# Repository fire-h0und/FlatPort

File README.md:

# FlatPort
Teensy 2.0 Risc-V dropin Arduino promicro lookalike with special features. The chip I used is [GD32 VF 103 CBT6](https://www.gigadevice.com/product/mcu/mcus-product-selector/gd32vf103cbt6) from Giga Device. 

It has a in-plane Type-C USB receptacle - it does not show much but it doubles as a full featured Type-C port - in this case a reversible USB 2.0 spec port only.

It also features in-plane Reset and Boot0 tasters - they are shorted by touching with a pointy conductive/metal object.<br>
  Do note they are not to be touched mutually by a same metal object: one shorts pin Boot0 to ground the other pulls the reset pin to Vcc.<br>
  In effect this means one of the contacts is gound and the other is Vcc - shorting them mutually would blow the fuse!

I picked to make this project for the alleged compatibility with QMK firmware - to be a future keyboard daughter board.
As I get to that point expect more updates here, it is on my ever growing TODO list :o}

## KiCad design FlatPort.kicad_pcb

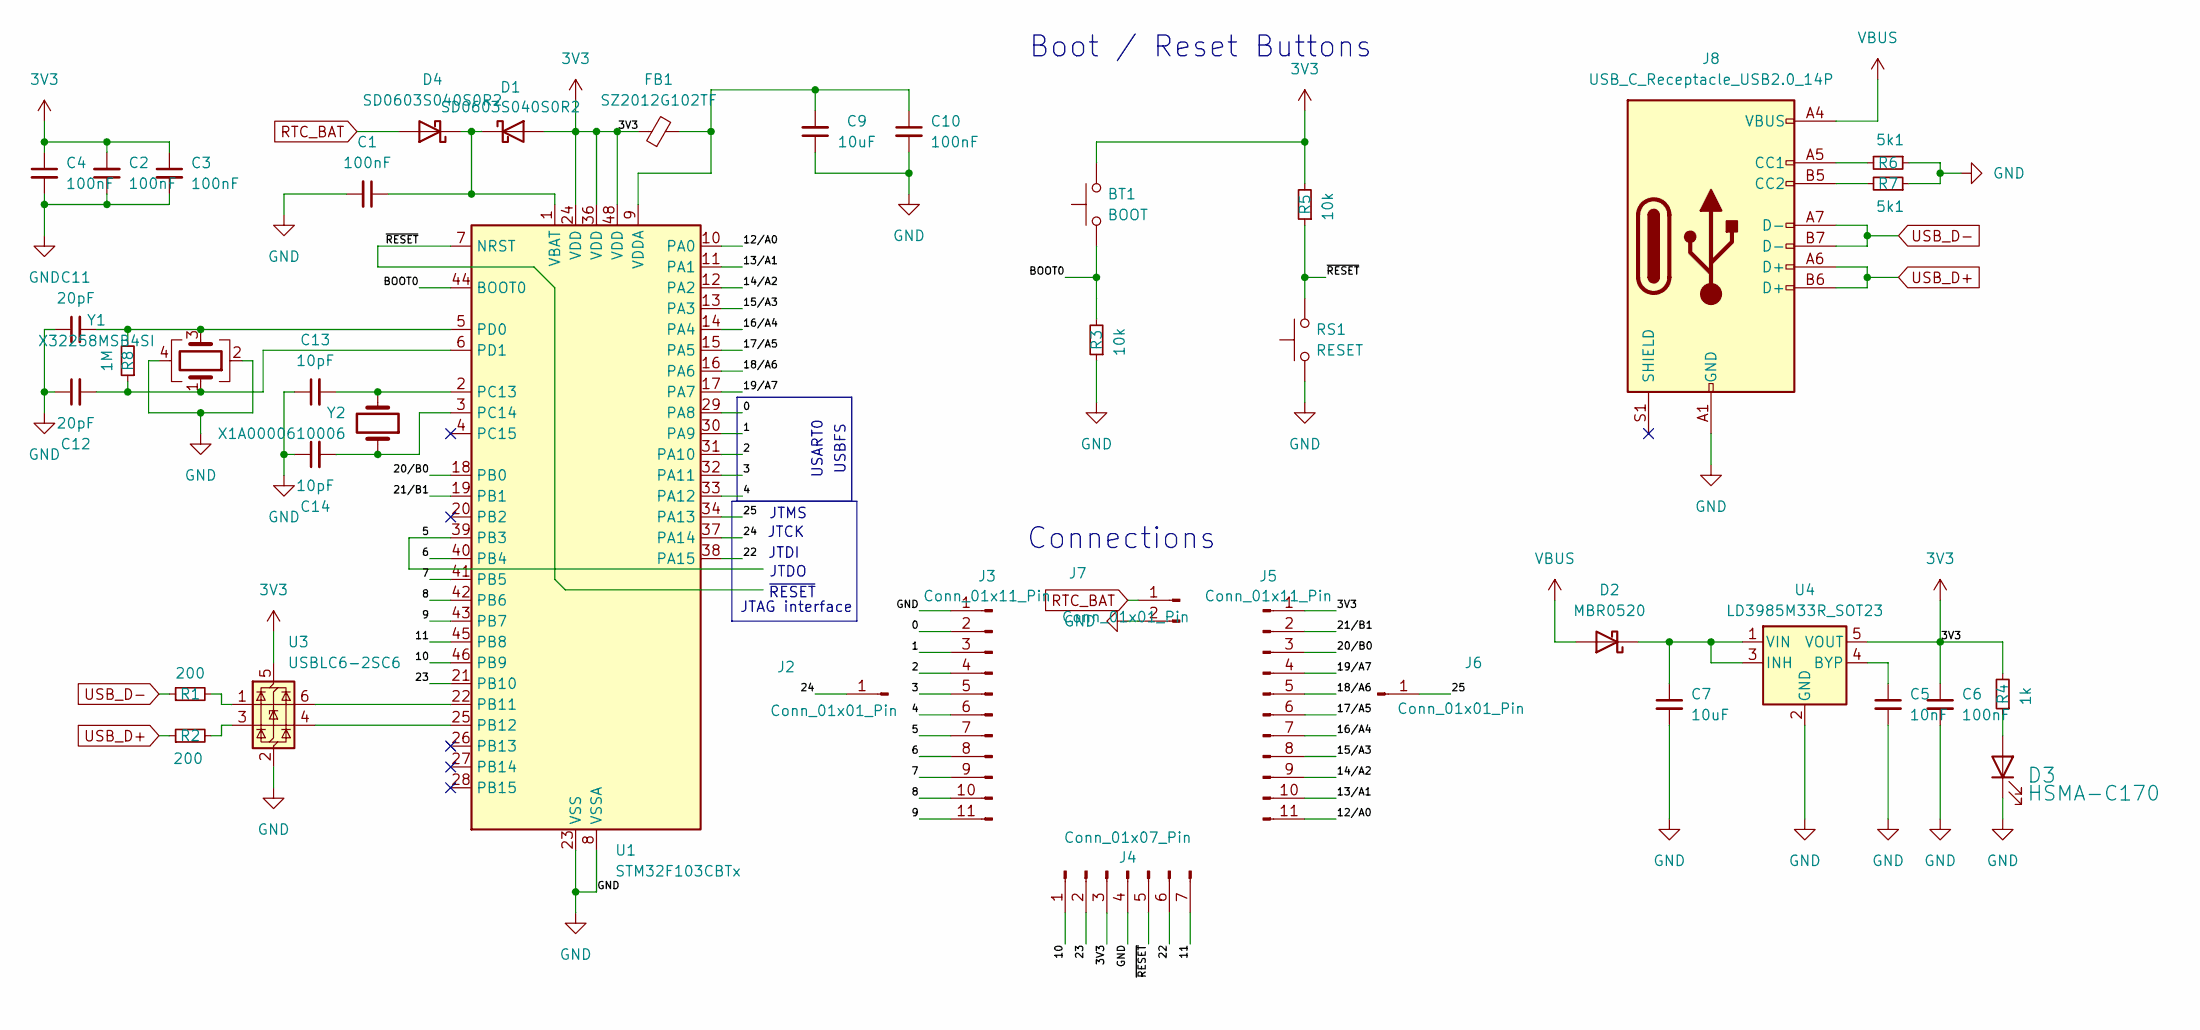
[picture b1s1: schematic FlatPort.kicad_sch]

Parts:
BT1: BOOT; Switch_Hole_1.0mm
C1, C2, C3, C4, C6, C10: 100nF; C_0402_1005Metric
C5: 10nF; C_0402_1005Metric
C7, C9: 10uF; C_0402_1005Metric
C11, C12: 20pF; C_0402_1005Metric
C13, C14: 10pF; C_0402_1005Metric
D1, D4: SD0603S040S0R2; D_0603_1608Metric
D2: MBR0520; D_SOD-123
D3: HSMA-C170; LED_0805_2012Metric
FB1: SZ2012G102TF; L_0805_2012Metric; LCSC Part# C1002
J2, J6: Conn_01x01_Pin; PinHeader_1x01_P2.54mm_Vertical
J3, J5: Conn_01x11_Pin; PinHeader_1x11_P2.54mm_Vertical
J4: Conn_01x07_Pin; PinHeader_1x07_P2.54mm_Vertical
J7: Conn_01x01_Pin; PinHeader_1x02_P1.27mm_Vertical
J8: USB_C_Receptacle_USB2.0_14P; TypeC_PCB_cutout
R1, R2: 200; R_0402_1005Metric
R3, R5: 10k; R_0402_1005Metric
R4: 1k; R_0402_1005Metric
R6, R7: 5k1; R_0402_1005Metric
R8: 1M; R_0402_1005Metric
RS1: RESET; Switch_Hole_1.0mm
U1: STM32F103CBTx; LQFP-48_7x7mm_P0.5mm
U3: USBLC6-2SC6; SOT-23-6
U4: LD3985M33R_SOT23; SOT-23-5
Y1: X32258MSB4SI; Crystal_SMD_3225-4Pin_3.2x2.5mm
Y2: X1A0000610006; Crystal_SMD_2012-2Pin_2.0x1.2mm

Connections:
3V3: BT1.2, C2.2, C3.1, C4.1, C6.1, D1.2 (A), FB1.1, J4.3, J5.1, R4.2, R5.2, U1.24 (VDD), U1.36 (VDD), U1.48 (VDD), U3.5 (VBUS), U4.5 (VOUT)
/0: J3.2, U1.29 (PA8)
/1: J3.3, U1.30 (PA9)
/2: J3.4, U1.31 (PA10)
/3: J3.5, U1.32 (PA11)
/4: J3.6, U1.33 (PA12)
/5: J3.7, U1.39 (PB3)
/6: J3.8, U1.40 (PB4)
/7: J3.9, U1.41 (PB5)
/8: J3.10, U1.42 (PB6)
/9: J3.11, U1.43 (PB7)
/10: J4.1, U1.46 (PB9)
/11: J4.7, U1.45 (PB8)
/12/A0: J5.11, U1.10 (PA0)
/13/A1: J5.10, U1.11 (PA1)
/14/A2: J5.9, U1.12 (PA2)
/15/A3: J5.8, U1.13 (PA3)
/16/A4: J5.7, U1.14 (PA4)
/17/A5: J5.6, U1.15 (PA5)
/18/A6: J5.5, U1.16 (PA6)
/19/A7: J5.4, U1.17 (PA7)
/20/B0: J5.3, U1.18 (PB0)
/21/B1: J5.2, U1.19 (PB1)
/22: J4.6, U1.38 (PA15)
/23: J4.2, U1.21 (PB10)
/24: J2.1, U1.37 (PA14)
/25: J6.1, U1.34 (PA13)
/BOOT0: BT1.1, R3.2, U1.44 (BOOT0)
/~RESET: J4.5, R5.1, RS1.2, U1.7 (NRST)
GND: C1.2, C2.1, C3.2, C4.2, C5.2, C6.2, C7.2, C9.1, C10.2, C11.1, C12.1, C13.1, C14.1, D3.1 (K), J3.1, J4.4, J7.2, J8.A1 (GND), J8.A12 (GND), J8.B1 (GND), J8.B12 (GND), R3.1, R6.1, R7.1, RS1.1, U1.8 (VSSA), U1.23 (VSS), U1.35 (VSS), U1.47 (VSS), U3.2 (GND), U4.2 (GND), Y1.2, Y1.4
unnamed: C1.1, D1.1 (K), D4.1 (K), U1.1 (VBAT)
unnamed: C7.1, D2.1 (K), U4.1 (VIN), U4.3 (INH)
unnamed: D3.2 (A), R4.1
unnamed: J8.A5 (CC1), R6.2
unnamed: J8.B5 (CC2), R7.2
unnamed: R1.2, U3.1 (I/O1)
unnamed: R2.2, U3.3 (I/O2)
unnamed: U1.22 (PB11), U3.6 (I/O1)
unnamed: U1.25 (PB12), U3.4 (I/O2)
unnamed: C13.2, U1.2 (PC13), Y2.2
unnamed: C14.2, U1.3 (PC14), Y2.1
unnamed: C11.2, R8.2, U1.5 (PD0), Y1.3
unnamed: C12.2, R8.1, U1.6 (PD1), Y1.1
unnamed: C9.2, C10.1, FB1.2, U1.9 (VDDA)
unnamed: C5.1, U4.4 (BYP)
RTC_BAT: D4.2 (A), J7.1
USB_D+: J8.A6 (D+), J8.B6 (D+), R2.1
USB_D-: J8.A7 (D-), J8.B7 (D-), R1.1
VBUS: D2.2 (A), J8.A4 (VBUS), J8.A9 (VBUS), J8.B4 (VBUS), J8.B9 (VBUS)

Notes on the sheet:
Boot / Reset Buttons
Connections
JTMS
USBFS
JTCK
~{RESET}
USART0
JTAG interface
JTDI
JTDO

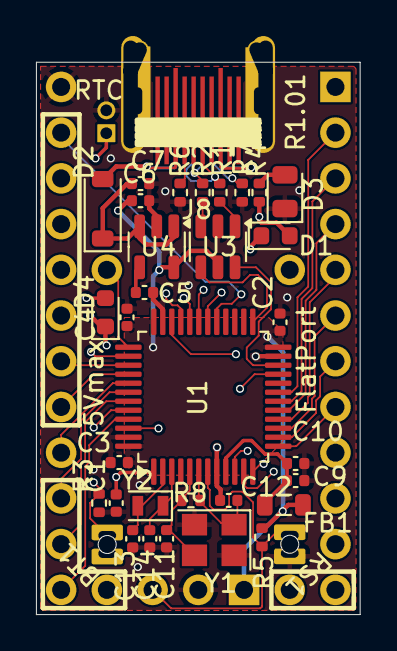
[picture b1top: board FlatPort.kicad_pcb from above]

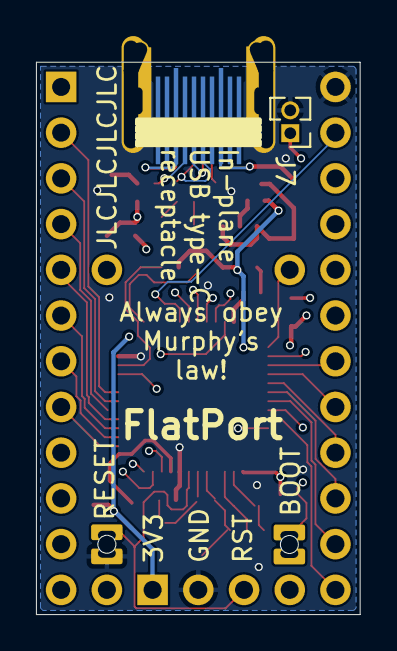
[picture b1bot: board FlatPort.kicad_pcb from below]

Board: 4 copper layers, 18.0 x 30.7 mm, 40 parts (6 on the bottom side), 49 nets.

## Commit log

2025-01-11 The R1.03 source files that actually had been sent for production
    This is the first build release
2025-01-11 i think this file has the missing footprints
2025-01-11 Create dummy.md
    temporary file
2025-01-11 The photos of the FlatPort
    Manufactured at JLCPCB and hand soldered the MCU in my shop
2025-01-11 Update README.md with pics
2025-01-11 Update README.md with more pics
2025-01-11 Update README.md
    added QMK compatibility note
2025-01-11 Update README.md
    Added the chip used and link
2025-01-12 Update README.md
    Fixed typos
